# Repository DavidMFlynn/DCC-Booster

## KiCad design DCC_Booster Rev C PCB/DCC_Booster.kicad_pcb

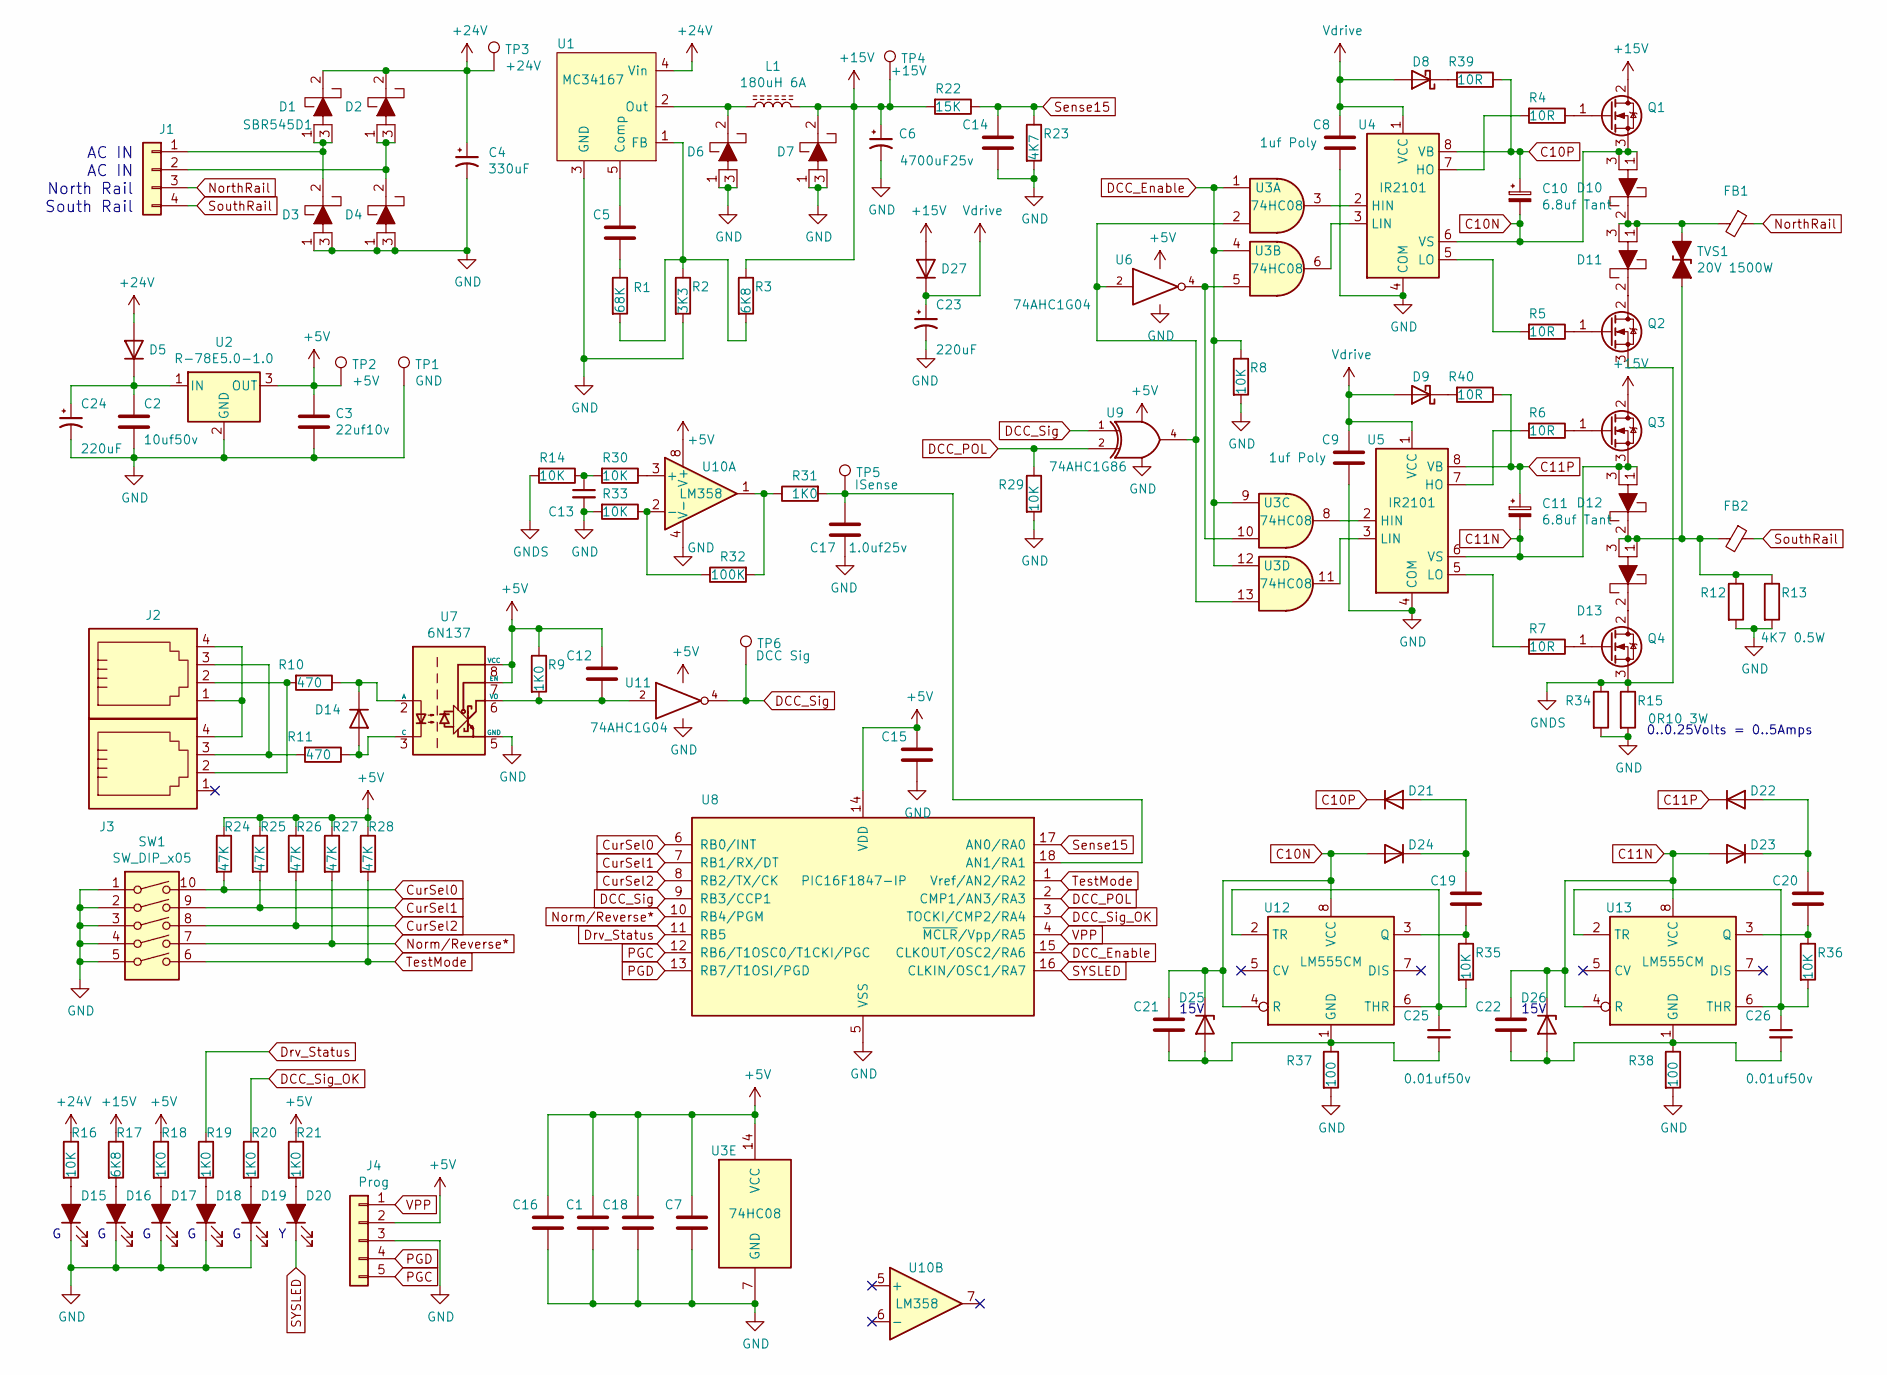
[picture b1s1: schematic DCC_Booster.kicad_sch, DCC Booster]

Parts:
C1, C5, C7, C12, C13, C14, C15, C16, C18, C19, C20, C21, C22: 0.1uf50v; C_0805_2012Metric_Pad1.15x1.40mm_HandSolder
C2: 10uf50v; C_1210_3225Metric_Pad1.42x2.65mm_HandSolder
C3: 22uf10v; C_1210_3225Metric_Pad1.42x2.65mm_HandSolder
C4: 330uF; CP_Radial_D18.0mm_P7.50mm
C6: 4700uF25v; CP_Radial_D18.0mm_P7.50mm
C8, C9: 1uf Poly; C_Rect_L7.0mm_W6.0mm_P5.00mm
C10, C11: 6.8uf Tant; CP_EIA-3528-21_Kemet-B_Pad1.50x2.35mm_HandSolder
C17: 1.0uf25v; C_0805_2012Metric_Pad1.15x1.40mm_HandSolder
C23, C24: 220uF; CP_Elec_10x10
C25, C26: 0.01uf50v; C_0805_2012Metric_Pad1.15x1.40mm_HandSolder
D1, D2, D3, D4, D6, D7, D10, D11, D12, D13: SBR545D1; TO-252-2
D5, D27: MRA4003T3G; D_SMA
D8, D9: B140-E3; D_SOD-123
D14: 1N4148; D_SOD-123
D15, D16, D17, D18, D19, D20: LED_ALT; LED_D3.0mm
D21, D22, D23, D24: 1N4148W; D_SOD-123
D25, D26: BZT52C15; D_SOD-123
FB1, FB2: Ferrite_Bead; L_1812_4532Metric_Pad1.30x3.40mm_HandSolder
J1: Conn_01x04; PhoenixContact_MC_1,5_4-G-5.08_1x04_P5.08mm_Horizontal
J2, J3: 4P4C; RJ9
J4: Prog; PinHeader_1x05_P2.54mm_Vertical
L1: 180uH 6A; L_Radial_D24.4mm_P23.70mm_muRATA_1400series
Q1, Q2, Q3, Q4: Q_NMOS_GDS; TO-252-2
R1: 68K; R_0805_2012Metric_Pad1.15x1.40mm_HandSolder
R2: 3K3; R_0805_2012Metric_Pad1.15x1.40mm_HandSolder
R3, R17: 6K8; R_0805_2012Metric_Pad1.15x1.40mm_HandSolder
R4, R5, R6, R7, R39, R40: 10R; R_0805_2012Metric_Pad1.15x1.40mm_HandSolder
R8, R14, R16, R29, R30, R33, R35, R36: 10K; R_0805_2012Metric_Pad1.15x1.40mm_HandSolder
R9, R18, R19, R20, R21, R31: 1K0; R_0805_2012Metric_Pad1.15x1.40mm_HandSolder
R10, R11: 470; R_0805_2012Metric_Pad1.15x1.40mm_HandSolder
R12, R13: 4K7 0.5W; R_1812_4532Metric_Pad1.30x3.40mm_HandSolder
R15, R34: 0R10 3W; R_2512_6332Metric_Pad1.52x3.35mm_HandSolder
R22: 15K; R_0805_2012Metric_Pad1.15x1.40mm_HandSolder
R23: 4K7; R_0805_2012Metric_Pad1.15x1.40mm_HandSolder
R24, R25, R26, R27, R28: 47K; R_0805_2012Metric_Pad1.15x1.40mm_HandSolder
R32: 100K; R_0805_2012Metric_Pad1.15x1.40mm_HandSolder
R37, R38: 100; R_0805_2012Metric_Pad1.15x1.40mm_HandSolder
SW1: SW_DIP_x05; SW_DIP_SPSTx05_Piano_10.8x14.26mm_W7.62mm_P2.54mm
TP1: GND; TestPoint_Pad_D2.0mm
TP2: +5V; TestPoint_Pad_D2.0mm
TP3: +24V; TestPoint_Pad_D2.0mm
TP4: +15V; TestPoint_Pad_D2.0mm
TP5: ISense; TestPoint_Pad_D2.0mm
TP6: DCC Sig; TestPoint_Pad_D2.0mm
TVS1: 20V 1500W; D_SMA-SMB_Universal_Handsoldering
U1: MC34167; TO-220-5_P3.4x3.7mm_StaggerOdd_Lead3.8mm_Vertical
U2: R-78E5.0-1.0; Converter_DCDC_RECOM_R-78E-0.5_THT
U3: 74HC08; SOIC-14_3.9x8.7mm_P1.27mm
U4, U5: IR2101; SOIC-8_3.9x4.9mm_P1.27mm
U6, U11: 74AHC1G04; TSOP-5_1.65x3.05mm_P0.95mm
U7: 6N137; SOIC-8_3.9x4.9mm_P1.27mm
U8: PIC16F1847-IP; SOIC-18W_7.5x11.6mm_P1.27mm
U9: 74AHC1G86; TSOP-5_1.65x3.05mm_P0.95mm
U10: LM358; SOIC-8_3.9x4.9mm_P1.27mm
U12, U13: LM555CM; SOIC-8_3.9x4.9mm_P1.27mm

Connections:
+5V: C1.1, C3.1, C7.1, C12.1, C15.1, C16.1, C18.1, J4.2, R9.1, R18.1, R21.1, R24.1, R25.1, R26.1, R27.1, R28.1, TP2.1, U2.3 (OUT), U3.14 (VCC), U6.5 (VCC), U7.7 (EN), U7.8 (VCC), U8.14 (VDD), U9.5 (VCC), U10.8 (V+), U11.5 (VCC)
+15V: C6.1, D7.2 (K), D27.2 (A), L1.2, Q1.2 (D), Q3.2 (D), R3.1, R17.1, R22.2, TP4.1
+24V: C4.1, D1.2 (K), D2.2 (K), D5.2 (A), R16.1, TP3.1, U1.4 (Vin)
C10N: C10.2, C21.1, D10.1 (A), D10.3 (A), D24.2 (A), D25.1 (K), Q1.3 (S), U4.6 (VS), U12.4 (R), U12.8 (VCC)
C10P: C10.1, D21.1 (K), R39.1, U4.8 (VB)
C11N: C11.2, C22.1, D12.1 (A), D12.3 (A), D23.2 (A), D26.1 (K), Q3.3 (S), U5.6 (VS), U13.4 (R), U13.8 (VCC)
C11P: C11.1, D22.1 (K), R40.1, U5.8 (VB)
CurSel0: R24.2, SW1.10, U8.6 (RB0/INT)
CurSel1: R25.2, SW1.9, U8.7 (RB1/RX/DT)
CurSel2: R26.2, SW1.8, U8.8 (RB2/TX/CK)
DCC_Enable: R8.1, U3.1, U3.4, U3.9, U3.12, U8.15 (CLKOUT/OSC2/RA6)
DCC_POL: R29.1, U8.2 (CMP1/AN3/RA3), U9.2
DCC_Sig: TP6.1, U8.9 (RB3/CCP1), U9.1, U11.4
DCC_Sig_OK: R20.1, U8.3 (TOCKI/CMP2/RA4)
Drv_Status: R19.1, U8.11 (RB5)
GND: C1.2, C2.2, C3.2, C4.2, C6.2, C7.2, C8.2, C9.2, C13.2, C14.2, C15.2, C16.2, C17.2, C18.2, C23.2, C24.2, D3.1 (A), D3.3 (A), D4.1 (A), D4.3 (A), D6.1 (A), D6.3 (A), D7.1 (A), D7.3 (A), D15.1 (K), D16.1 (K), D17.1 (K), D18.1 (K), D19.1 (K), J4.3, R2.2, R8.2, R12.2, R13.2, R15.2, R23.2, R29.2, R33.2, R34.2, R37.2, R38.2, SW1.1, SW1.2, SW1.3, SW1.4, SW1.5, TP1.1, U1.3 (GND), U2.2 (GND), U3.7 (GND), U4.4 (COM), U5.4 (COM), U6.3 (GND), U7.5 (GND), U8.5 (VSS), U9.3 (GND), U10.4 (V-), U11.3 (GND); also elsewhere on the board
GNDS: Q2.3 (S), Q4.3 (S), R14.2, R15.1, R34.1
unnamed: C2.1, C24.1, D5.1 (K), U2.1 (IN)
unnamed: C5.1, U1.5 (Comp)
unnamed: C5.2, R1.1
unnamed: C12.2, R9.2, U7.6 (VO), U11.2
unnamed: C13.1, R14.1, R30.2
unnamed: C17.1, R31.2, TP5.1, U8.18 (AN1/RA1)
unnamed: C19.1, D21.2 (A), D24.1 (K)
unnamed: C19.2, R35.1, U12.3 (Q)
unnamed: C20.1, D22.2 (A), D23.1 (K)
unnamed: C20.2, R36.1, U13.3 (Q)
unnamed: C21.2, C25.2, D25.2 (A), R37.1, U12.1 (GND)
unnamed: C22.2, C26.2, D26.2 (A), R38.1, U13.1 (GND)
unnamed: C25.1, R35.2, U12.2 (TR), U12.6 (THR)
unnamed: C26.1, R36.2, U13.2 (TR), U13.6 (THR)
unnamed: D1.1 (A), D1.3 (A), D3.2 (K), J1.1
unnamed: D2.1 (A), D2.3 (A), D4.2 (K), J1.2
unnamed: D6.2 (K), L1.1, U1.2 (Out)
unnamed: D8.1 (K), R39.2
unnamed: D9.1 (K), R40.2
unnamed: D10.2 (K), D11.1 (A), D11.3 (A), FB1.2, TVS1.1 (A1)
unnamed: D11.2 (K), Q2.2 (D)
unnamed: D12.2 (K), D13.1 (A), D13.3 (A), FB2.2, R12.1, R13.1, TVS1.2 (A2)
unnamed: D13.2 (K), Q4.2 (D)
unnamed: D14.1 (K), R10.1, U7.2 (A)
unnamed: D14.2 (A), R11.1, U7.3 (C)
unnamed: D15.2 (A), R16.2
unnamed: D16.2 (A), R17.2
unnamed: D17.2 (A), R18.2
unnamed: D18.2 (A), R19.2
unnamed: D19.2 (A), R20.2
unnamed: D20.2 (A), R21.2
unnamed: J2.1, J2.4, J3.4
unnamed: J2.2, J3.2, R10.2
unnamed: J2.3, J3.3, R11.2
unnamed: Q1.1 (G), R4.1
unnamed: Q2.1 (G), R5.1
unnamed: Q3.1 (G), R6.1
unnamed: Q4.1 (G), R7.1
unnamed: R1.2, R2.1, R3.2, U1.1 (FB)
unnamed: R4.2, U4.7 (HO)
unnamed: R5.2, U4.5 (LO)
unnamed: R6.2, U5.7 (HO)
unnamed: R7.2, U5.5 (LO)
unnamed: R30.1, U10.3 (+)
unnamed: R31.1, R32.2, U10.1
unnamed: R32.1, R33.1, U10.2 (-)
unnamed: U3.3, U4.2 (HIN)
unnamed: U3.6, U4.3 (LIN)
unnamed: U3.8, U5.2 (HIN)
unnamed: U3.5, U3.10, U6.4
unnamed: U3.11, U5.3 (LIN)
unnamed: U3.2, U3.13, U6.2, U9.4
Norm/Reverse*: R27.2, SW1.7, U8.10 (RB4/PGM)
NorthRail: FB1.1, J1.3
PGC: J4.5, U8.12 (RB6/T1OSC0/T1CKI/PGC)
PGD: J4.4, U8.13 (RB7/T1OSI/PGD)
SYSLED: D20.1 (K), U8.16 (CLKIN/OSC1/RA7)
Sense15: C14.1, R22.1, R23.1, U8.17 (AN0/RA0)
SouthRail: FB2.1, J1.4
TestMode: R28.2, SW1.6, U8.1 (Vref/AN2/RA2)
VPP: J4.1, U8.4 (~MCLR/Vpp/RA5)
Vdrive: C8.1, C9.1, C23.1, D8.2 (A), D9.2 (A), D27.1 (K), U4.1 (VCC), U5.1 (VCC)

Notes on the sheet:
AC IN AC IN North Rail South Rail
15V
0..0.25Volts = 0..5Amps

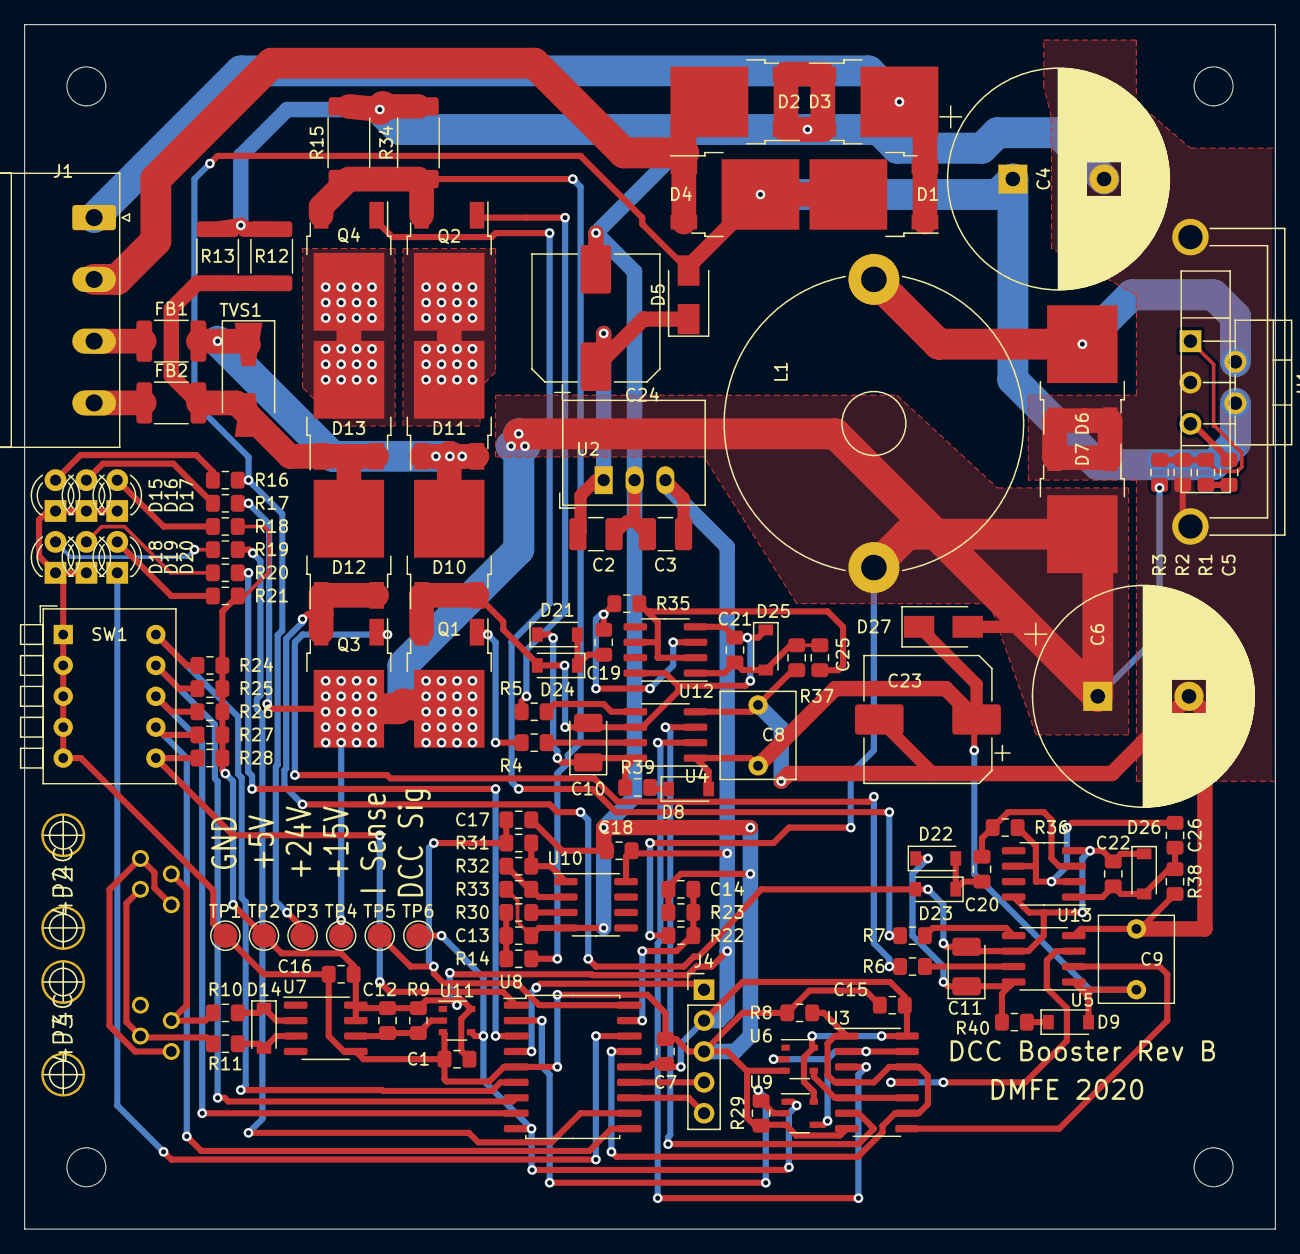
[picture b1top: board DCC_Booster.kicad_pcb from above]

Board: 2 copper layers, 102.9 x 99.1 mm, 130 parts (0 on the bottom side), 79 nets.

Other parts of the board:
H1, H2, H3, H4: MountingHole_3.2mm_M3
HS1: Heatsink_Fischer_FK224xx2201_25x8.3mm

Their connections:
GND: HS1.1; also elsewhere on the board

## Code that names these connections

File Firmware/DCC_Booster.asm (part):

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;     If over current or invalid signal disable driver, Error rate sys LED, clear dvr/sig LEDs.
;====================================================================================================
;
;   Pin 1 (RA2/AN2) SW5 (Active Low Input)
;   Pin 2 (RA3/AN3) DCC Polarity (Output)
;   Pin 3 (RA4/AN4) DCC Signal OK LED (Active High Output)
;   Pin 4 (RA5/MCLR*) VPP/MCLR*
;   Pin 5 (GND) Ground
;   Pin 6 (RB0) Current Select 0 (Active Low Input)
;   Pin 7 (RB1/AN11/SDA1) Current Select 1 (Active Low Input)
;   Pin 8 (RB2/AN10/TX) Current Select 2 (Active Low Input)
;   Pin 9 (RB3/CCP1) DCC Signal (Active High Input)
;
;   Pin 10 (RB4/AN8/SLC1) Normal/Reverse* (Active Low Input)
;   Pin 11 (RB5/AN7) Driver Status LED (Active High Output)
;   Pin 12 (RB6/AN5/CCP2) ICSPCLK
;   Pin 13 (RB7/AN6) ICSPDAT
;   Pin 14 (Vcc) +5 volts
;   Pin 15 (RA6) MOSFET Driver Enable (Active High Output)
;   Pin 16 (RA7/CCP2) System LED (Active Low Output)(System LED)
;   Pin 17 (RA0/AN0) 15V Sense analog input
;   Pin 18 (RA1/AN1) Current sensing analog input
;
;====================================================================================================
;
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; INTOSC oscillator: I/O function on CLKIN pin
; WDT Enabled
; PWRT Enabled
; MCLR/VPP pin function is digital input
; Program memory code protection is disabled
; Data memory code protection is disabled
; Brown-out Reset enabled
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#Define	SW5_In	PORTA,2	;SW5 Test Mode
#Define	DCC_Pole	LATA,3	;DCC Polarity (Output)
#Define	SigOK_LED	LATA,4	;DCC Signal OK LED (Active High Output)
#Define	RA5_In	PORTA,5	;VPP/MCLR*
#Define	Drv_Enable	LATA,6	;MOSFET Driver Enable (Active High Output)
#Define	RA7_In	PORTA,7	;System LED (Active Low Output)(System LED)
SysLED_Bit	EQU	7	;System LED (Active Low Output)
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
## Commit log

2019-11-09 first push
2019-11-09 worked on PCB
2019-11-10 pcb almost done
    needs labels
2019-11-12 PCB ordered
2020-01-10 parts
2020-01-12 begin firmware
2020-02-27 We have blink!
2020-02-28 Some code
2020-02-29 more new code
2020-02-29 Minimum functionality achived.
2020-03-06 started rev A
2020-03-07 Schematic Rev A
2020-03-08 Rev A PCB ordered
2020-03-12 Rev B
2020-03-19 Rev B PCB
2020-05-28 Parts list update
2020-06-11 get ignore
2020-07-02 Bug fix
2020-07-03 1.0d4
2020-07-25 Adding F/R
2020-08-14 looking for shut down
2021-07-31 Updated Config
2021-07-31 Began Rev C PCB
